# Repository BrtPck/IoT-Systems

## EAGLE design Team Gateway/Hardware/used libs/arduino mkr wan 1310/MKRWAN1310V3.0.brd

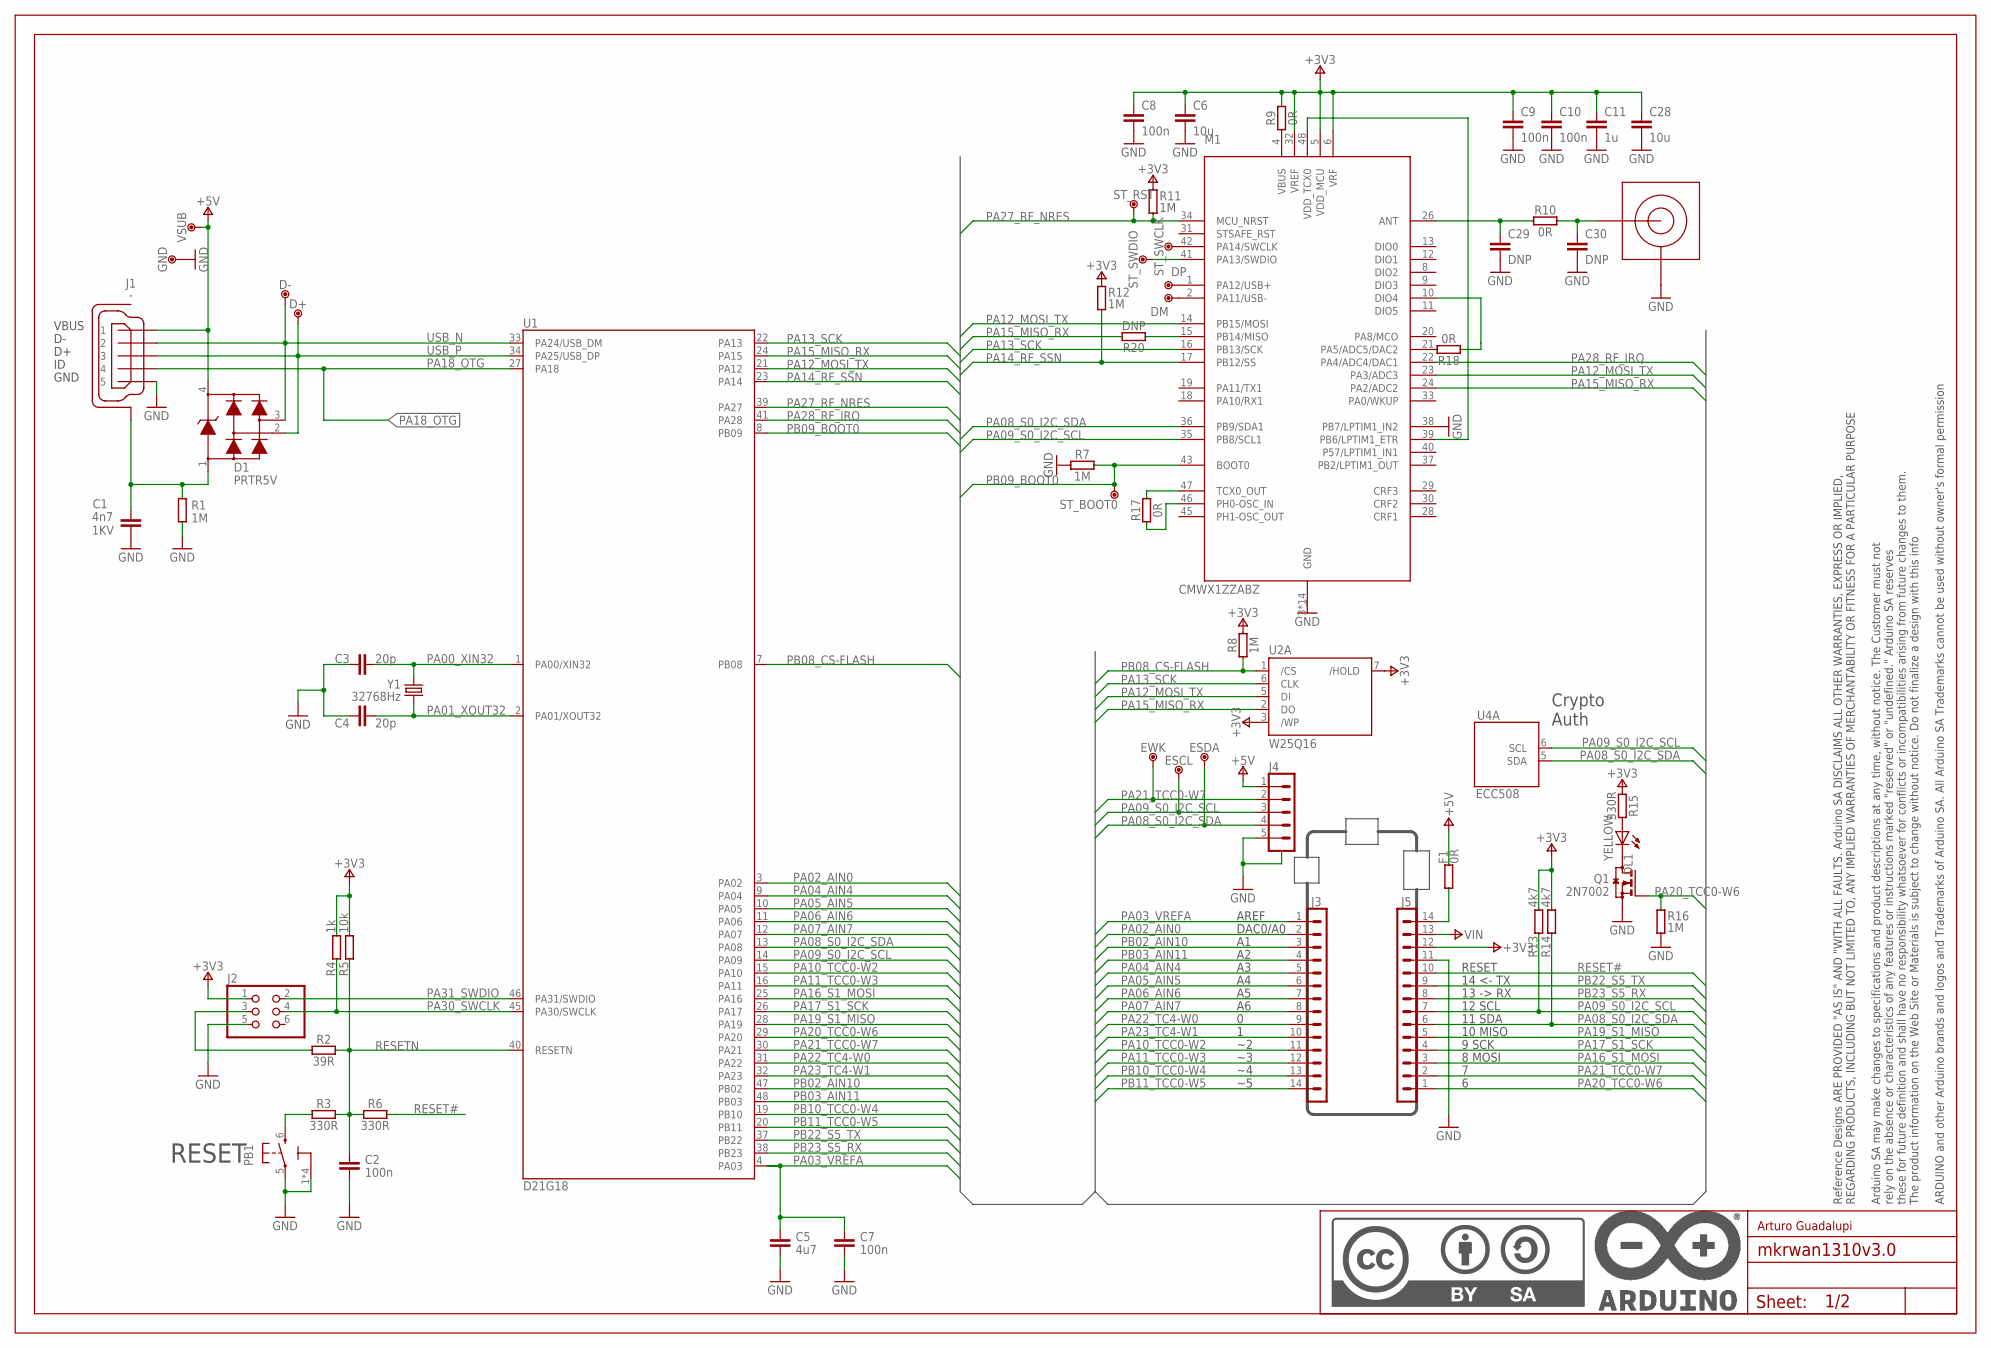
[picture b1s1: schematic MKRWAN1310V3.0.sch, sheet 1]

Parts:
C1: 4n7; 0805-R2013X50N; VOLTAGE 1KV
C2, C7, C8, C9, C10: 100n; 0402-1005X55N
C3, C4: 20p; 0402-1005X55N
C5: 4u7; 0402-1005X55N
C6, C28: 10u; 0603-1608X90N
C11: 1u; 0402-1005X55N
C29, C30: DNP; 0402-1005X55N
D1: PRTR5V; SOT190P230X110-4N
D+: DNP; TP-1.00MM
D-: DNP; TP-1.00MM
DL1: YELLOW; LEDC1608X80N-AK
DM: DNP; TP-1.27MM
DP: DNP; TP-1.27MM
ESCL: DNP; TP-1.00MM
ESDA: DNP; TP-1.00MM
EWK: DNP; TP-1.00MM
F1: 0R; C0603
FRAME1: DNP; FRAME
GND: DNP; TP-1.00MM
J1: -; ZX62-AB-5PA
J2: DNP; 2X3_SMT
J3, J5: -; 1X14_SMD_TH
J4: -; SM05B-SRSS-TB
J8: -; U.FL-R-SMT-1(60)
M1: CMWX1ZZABZ
PB1: PTS820; C&K_PTS820_NO_HOLES
Q1: 2N7002; SOTFL50P160X78-3
R1, R7, R8, R11, R12, R16: 1M; 0402-1005X55N
R2: 39R; 0402-1005X55N
R3, R6, R15: 330R; 0402-1005X55N
R4: 1k; 0402-1005X55N
R5: 10k; 0402-1005X55N
R9, R10, R17, R18: 0R; 0402-1005X55N
R13, R14: 4k7; 0402-1005X55N
R20: DNP; 0402-1005X55N
ST_BOOT0: DNP; TP-0.8MM
ST_RST: DNP; TP-0.8MM
ST_SWCLK: DNP; TP-0.8MM
ST_SWDIO: DNP; TP-0.8MM
U1: D21G18; QFN50P700X700X90-49XN-EPSQ515
U2: W25Q16; SON9P127_500X600X80L60X41T340X400N
U4: ECC508; SON50P300X200X60-9N-EP160X140
VSUB: DNP; TP-1.00MM
Y1: 32768Hz; ABS07

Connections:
+3V3: C6.1, C8.1, C9.1, C10.1, C11.1, C28.1, J2.1, J5.12, M1.5 (VDD_MCU), M1.6 (VRF), M1.32 (VREF), R4.2, R5.2, R8.2, R9.2, R11.2, R12.2, R13.2, R14.2, R15.1, U2.3 (/WP), U2.7 (/HOLD); also elsewhere on the board
+5V: D1.4, F1.2, J1.1, J4.1, VSUB.X; also elsewhere on the board
GND: C1.2, C2.2, C3.1, C4.1, C5.2, C6.2, C7.2, C8.2, C9.2, C10.2, C11.2, C28.2, C29.2, C30.2, GND.X, J1.5, J2.5, J4.5, J4.SH1 (SH), J4.SH2 (SH), J5.11, J8.GND1 (GND), J8.GND2 (GND), M1.3 (GND), M1.7 (GND), M1.25 (GND), M1.27 (GND), M1.38 (PB7/LPTIM1_IN2), M1.44 (GND), M1.49 (GND), M1.50 (GND), M1.51 (GND), M1.52 (GND), M1.53 (GND), M1.54 (GND), M1.55 (GND), M1.56 (GND), M1.57 (GND), PB1.1 (3), PB1.2 (3), PB1.3, PB1.4 (3), PB1.5 (1), Q1.S, R1.1, R7.1, R16.1; also elsewhere on the board
N17658775: PB1.6 (2), R3.1
unnamed: C1.1, D1.1, J1.6 (SH), J1.7 (SH), J1.8 (SH), J1.9 (SH), J1.10 (SH), J1.11 (SH), R1.2
unnamed: F1.1, J5.14
unnamed: J2.3, R2.1
unnamed: M1.39 (PB6/LPTIM1_ETR), M1.48 (VDD_TCX0)
unnamed: C29.1, M1.26 (ANT), R10.1
unnamed: DL1.A, R15.2
unnamed: C30.1, J8.SIG, R10.2
unnamed: M1.4 (VBUS), R9.1
unnamed: DL1.C, Q1.D
unnamed: M1.42 (PA14/SWCLK), ST_SWCLK.X
unnamed: M1.41 (PA13/SWDIO), ST_SWDIO.X
unnamed: M1.47 (TCX0_OUT), R17.2
unnamed: M1.46 (PH0-OSC_IN), R17.1
unnamed: M1.21 (PA5/ADC5/DAC2), R18.2
unnamed: M1.10 (DIO4), R18.1
unnamed: DP.X, M1.1 (PA12/USB+)
unnamed: DM.X, M1.2 (PA11/USB-)
unnamed: M1.15 (PB14/MISO), R20.1
PA00_XIN32: C3.2, U1.1 (PA00/XIN32), Y1.2
PA01_XOUT32: C4.2, U1.2 (PA01/XOUT32), Y1.1
PA02_AIN0: J3.2, U1.3 (PA02)
PA03_VREFA: C5.1, C7.1, J3.1, U1.4 (PA03)
PA04_AIN4: J3.5, U1.9 (PA04)
PA05_AIN5: J3.6, U1.10 (PA05)
PA06_AIN6: J3.7, U1.11 (PA06)
PA07_AIN7: J3.8, U1.12 (PA07)
PA08_S0_I2C_SDA: ESDA.X, J4.4, J5.6, M1.36 (PB9/SDA1), R14.1, U1.13 (PA08), U4.5 (SDA); also elsewhere on the board
PA09_S0_I2C_SCL: ESCL.X, J4.3, J5.7, M1.35 (PB8/SCL1), R13.1, U1.14 (PA09), U4.6 (SCL); also elsewhere on the board
PA10_TCC0-W2: J3.11, U1.15 (PA10)
PA11_TCC0-W3: J3.12, U1.16 (PA11)
PA12_MOSI_TX: M1.14 (PB15/MOSI), M1.23 (PA3/ADC3), U1.21 (PA12), U2.5 (DI)
PA13_SCK: M1.16 (PB13/SCK), U1.22 (PA13), U2.6 (CLK)
PA14_RF_SSN: M1.17 (PB12/SS), R12.1, U1.23 (PA14)
PA15_MISO_RX: M1.24 (PA2/ADC2), R20.2, U1.24 (PA15), U2.2 (DO)
PA16_S1_MOSI: J5.3, U1.25 (PA16)
PA17_S1_SCK: J5.4, U1.26 (PA17)
PA18_OTG: J1.4, U1.27 (PA18); also elsewhere on the board
PA19_S1_MISO: J5.5, U1.28 (PA19)
PA20_TCC0-W6: J5.1, Q1.G, R16.2, U1.29 (PA20)
PA21_TCC0-W7: EWK.X, J4.2, J5.2, U1.30 (PA21)
PA22_TC4-W0: J3.9, U1.31 (PA22)
PA23_TC4-W1: J3.10, U1.32 (PA23)
PA27_RF_NRES: M1.34 (MCU_NRST), R11.1, ST_RST.X, U1.39 (PA27)
PA28_RF_IRQ: M1.22 (PA4/ADC4/DAC1), U1.41 (PA28)
PA30_SWCLK: J2.4, R4.1, U1.45 (PA30/SWCLK)
PA31_SWDIO: J2.2, U1.46 (PA31/SWDIO)
PB02_AIN10: J3.3, U1.47 (PB02)
PB03_AIN11: J3.4, U1.48 (PB03)
PB08_CS-FLASH: R8.1, U1.7 (PB08), U2.1 (/CS)
PB09_BOOT0: M1.43 (BOOT0), R7.2, ST_BOOT0.X, U1.8 (PB09)
PB10_TCC0-W4: J3.13, U1.19 (PB10)
PB11_TCC0-W5: J3.14, U1.20 (PB11)
PB22_S5_TX: J5.9, U1.37 (PB22)
PB23_S5_RX: J5.8, U1.38 (PB23)
RESET#: J5.10, R6.2
RESETN: C2.1, R2.2, R3.2, R5.1, R6.1, U1.40 (RESETN)
USB_N: D1.3, D-.X, J1.2, U1.33 (PA24/USB_DM)
USB_P: D1.2, D+.X, J1.3, U1.34 (PA25/USB_DP)
VIN: J5.13; also elsewhere on the board

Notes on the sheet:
14 <- TX
13 -> RX
12 SCL
RESET
11 SDA
8 MOSI
9 SCK
10 MISO
AREF
DAC0/A0
Crypto Auth
Arturo Guadalupi

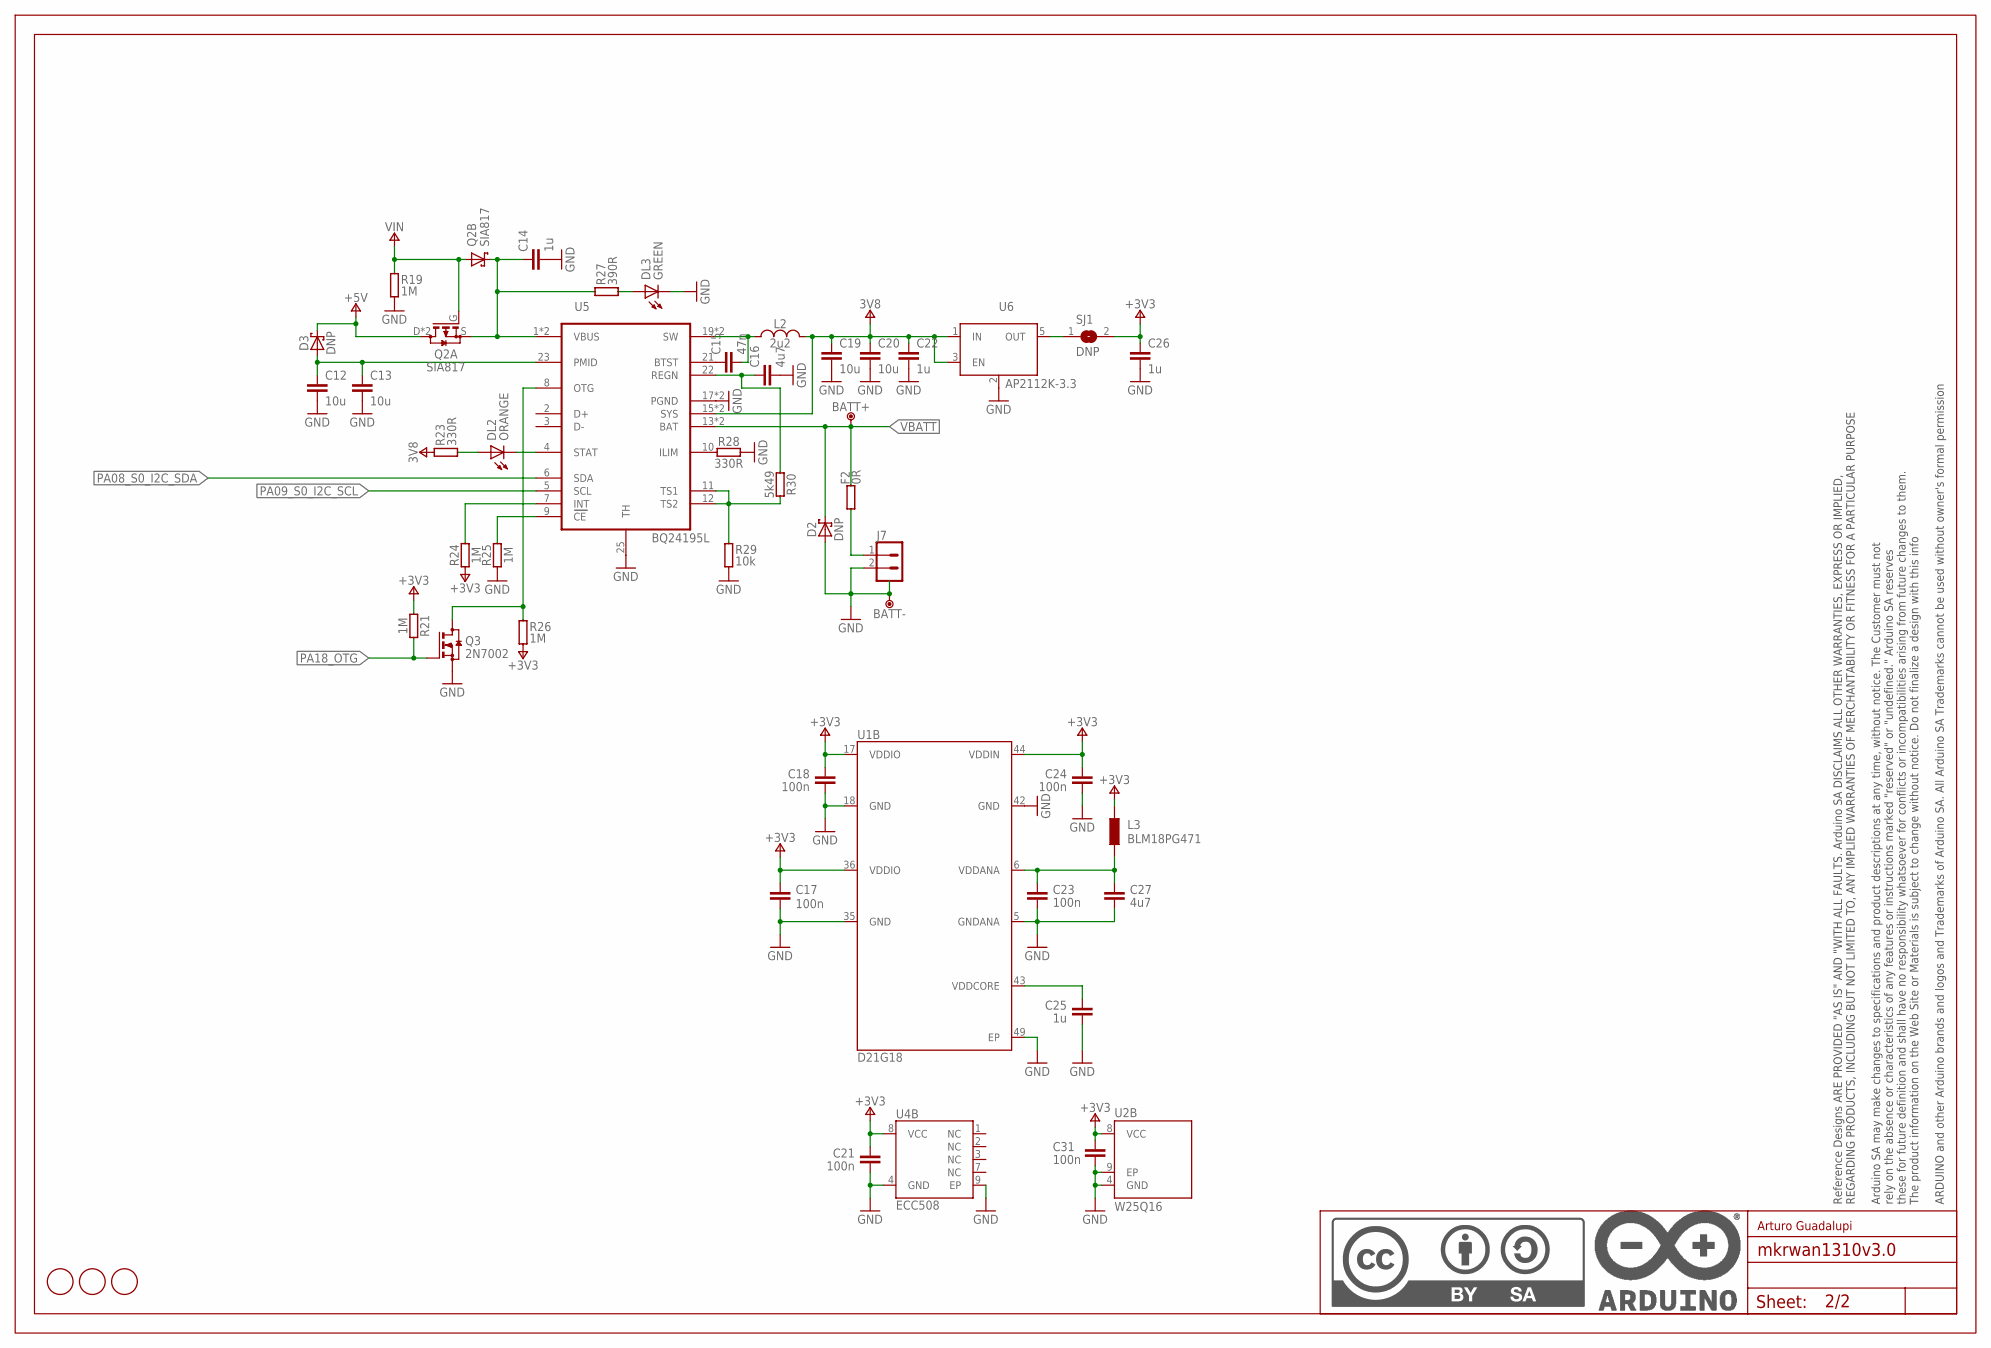
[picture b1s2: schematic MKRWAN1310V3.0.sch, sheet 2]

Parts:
BATT+: DNP; TP-1.00MM
BATT-: DNP; TP-1.00MM
C12, C13, C19, C20: 10u; 0603-1608X90N
C14, C22, C25, C26: 1u; 0402-1005X55N
C15: 47n; 0402-1005X55N
C16: 4u7; 0402-1005X55N
C17, C18, C21, C23, C24, C31: 100n; 0402-1005X55N
C27: 4u7; 0603-1608X90N
D2, D3: DNP; SODFL3517X110N
DL2: ORANGE; LEDC1608X80N-AK
DL3: GREEN; LEDC1608X80N-AK
F2: 0R; C0603
FD1, FD2, FD3: DNP; FD-1-1.5
FRAME2: DNP; FRAME
J7: -; JST-S2B-PH-SM4-TB
L2: 2u2; SRP4020
L3: BLM18PG471; 0603-1608X90N
Q2: SIA817; SON65P205X205X75-8N-MWSD
Q3: 2N7002; SOTFL50P160X78-3
R19, R21, R24, R25, R26: 1M; 0402-1005X55N
R23, R28: 330R; 0402-1005X55N
R27: 390R; 0402-1005X55N
R29: 10k; 0402-1005X55N
R30: 5k49; 0402-1005X55N
SJ1: DNP; SJ
U1: D21G18; QFN50P700X700X90-49XN-EPSQ515
U2: W25Q16; SON9P127_500X600X80L60X41T340X400N
U4: ECC508; SON50P300X200X60-9N-EP160X140
U5: BQ24195L; QFN24
U6: AP2112K-3.3; SOT25

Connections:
+3V3: C17.1, C18.1, C21.1, C24.1, C26.1, C31.2, L3.1, R21.1, R24.1, R26.1, SJ1.2, U1.17 (VDDIO), U1.36 (VDDIO), U1.44 (VDDIN), U2.8 (VCC), U4.8 (VCC); also elsewhere on the board
+3V8: C19.1, C20.1, C22.1, L2.2, R23.2, U5.15 (SYS), U5.16 (SYS), U6.1 (IN), U6.3 (EN)
+5V: D3.C, Q2.D, Q2.D2 (D); also elsewhere on the board
GND: BATT-.X, C12.2, C13.2, C14.2, C16.2, C17.2, C18.2, C19.2, C20.2, C21.2, C22.2, C23.2, C24.2, C25.2, C26.2, C27.2, C31.1, D2.A, DL3.C, J7.2, J7.3 (SH), J7.4 (SH), Q3.S, R19.1, R25.1, R28.2, R29.1, U1.5 (GNDANA), U1.18 (GND), U1.35 (GND), U1.42 (GND), U1.49 (EP), U2.4 (GND), U2.9 (EP), U4.4 (GND), U4.9 (EP), U5.17 (PGND), U5.18 (PGND), U5.25 (TH), U6.2 (GND/ADJ); also elsewhere on the board
N17798864: DL2.A, R23.1
N17834267: DL3.A, R27.1
N17852357: C23.1, C27.1, L3.2, U1.6 (VDDANA)
N17852431: C25.1, U1.43 (VDDCORE)
unnamed: F2.1, J7.1
unnamed: C15.2, L2.1, U5.19 (SW), U5.20 (SW)
unnamed: C14.1, Q2.K (C), Q2.K2 (C), Q2.S, R27.2, U5.1 (VBUS), U5.24 (VBUS)
unnamed: C15.1, U5.21 (BTST)
unnamed: R28.1, U5.10 (ILIM)
unnamed: C16.1, R30.1, U5.22 (REGN)
unnamed: Q3.D, R26.2, U5.8 (OTG)
unnamed: R29.2, R30.2, U5.11 (TS1), U5.12 (TS2)
unnamed: R25.2, U5.9 (CE)
unnamed: SJ1.1, U6.5 (OUT)
PA08_S0_I2C_SDA: U5.6 (SDA); also elsewhere on the board
PA09_S0_I2C_SCL: U5.5 (SCL); also elsewhere on the board
PA18_OTG: Q3.G, R21.2; also elsewhere on the board
PMICINT: R24.2, U5.7 (INT)
STAT: DL2.C, U5.4 (STAT)
VBATT: BATT+.X, D2.C, F2.2, U5.13 (BAT), U5.14 (BAT)
VIN: Q2.A, Q2.G, R19.2; also elsewhere on the board
VUSB1: C12.1, C13.1, D3.A, U5.23 (PMID)

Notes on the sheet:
Arturo Guadalupi

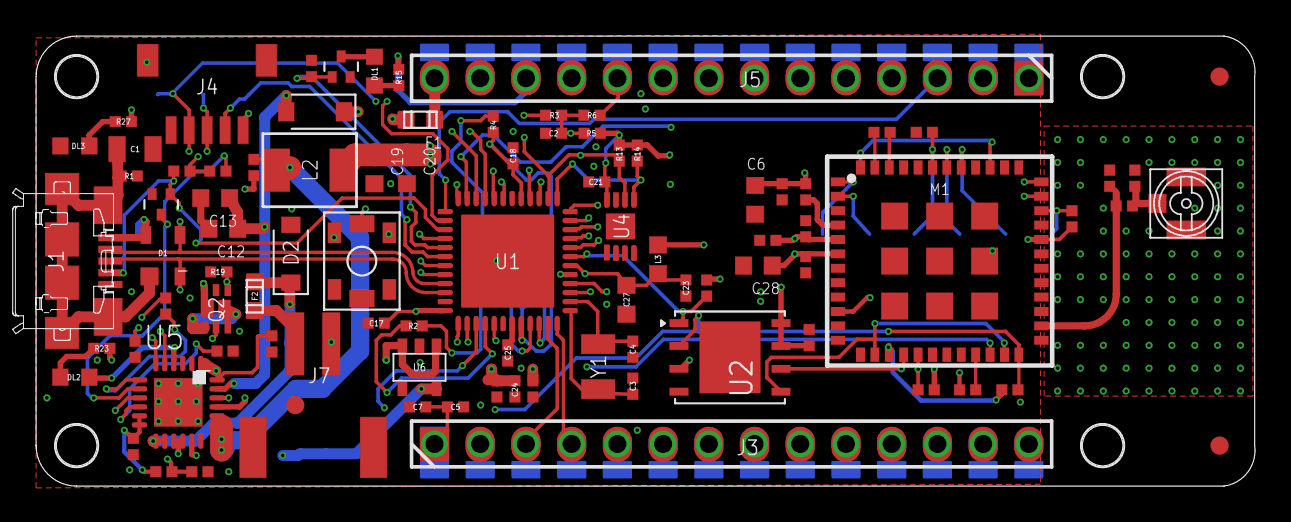
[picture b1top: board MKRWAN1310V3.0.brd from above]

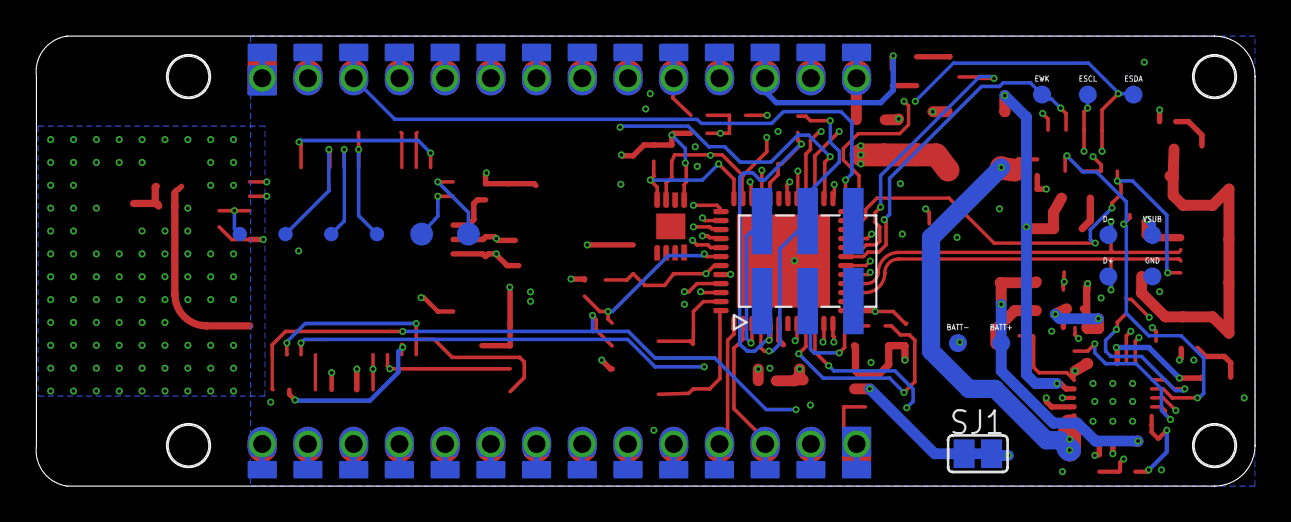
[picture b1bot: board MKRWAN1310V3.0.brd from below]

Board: 4 copper layers, 67.7 x 25.0 mm, 113 parts (2 on the bottom side), 82 nets.

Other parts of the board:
U$5, U$6, U$7, U$8: MH_RND_F_2.2MM_NM

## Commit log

2024-12-18 Create test
2024-12-18 Delete test
    delete test files
2024-12-18 Create datalayout
2024-12-18 update hardware files NODE
2024-12-18 Added files from team Posture
2024-12-18 kicad gateway
2024-12-19 Add files via upload
    add node code, lora library changes and heartrate debugger
2024-12-19 Rename main.cpp to nodeCode.cpp

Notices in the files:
Team Gateway/Hardware/used libs/arduino mkr wan 1310/MKRWAN1310V3.0.brd:
Copyright (c) 2016-2017 Arduino LLC.  All right reserved. EAGLE Design Rules
parts and their libraries:
Arduino-ucs: Copyright (c) 2016-2017 Arduino LLC.  All right reserved.
